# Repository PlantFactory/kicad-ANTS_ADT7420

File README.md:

# kicad-ANTS_ADT7420

ANTS ADT7420 dry/wet temperature sensor compatible board using ADT7420.

However, it is very difficult to apply soldering for ADT7420.

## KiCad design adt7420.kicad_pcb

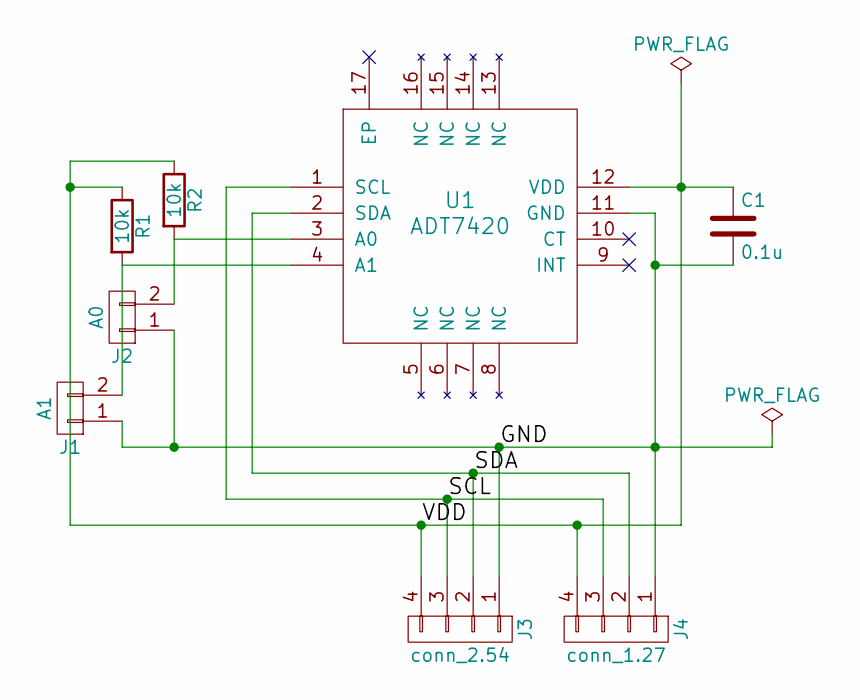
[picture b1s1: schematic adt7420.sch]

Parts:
C1: 0.1u; C_0603_HandSoldering
J1: A1; Pin_Header_Straight_2x01_Pitch1.27mm
J2: A0; Pin_Header_Straight_2x01_Pitch1.27mm
J3: conn_2.54; Pin_Header_Straight_1x04_Pitch2.54mm
J4: conn_1.27; Pin_Header_Straight_1x04_Pitch1.27mm
R1, R2: 10k; R_0603_HandSoldering
U1: ADT7420

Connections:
/GND: C1.2, J1.1, J2.1, J3.1, J4.1, U1.11 (GND)
/SCL: J3.3, J4.3, U1.1 (SCL)
/SDA: J3.2, J4.2, U1.2 (SDA)
/VDD: C1.1, J3.4, J4.4, R1.1, R2.1, U1.12 (VDD)
unnamed: J1.2, R1.2, U1.4 (A1)
unnamed: J2.2, R2.2, U1.3 (A0)

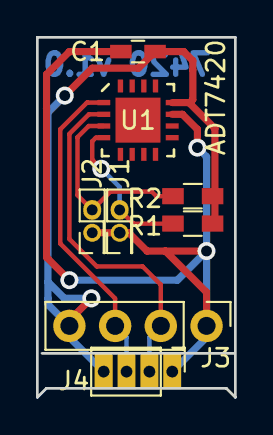
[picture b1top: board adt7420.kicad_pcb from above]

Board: 2 copper layers, 11.0 x 20.0 mm, 8 parts (0 on the bottom side), 6 nets.
